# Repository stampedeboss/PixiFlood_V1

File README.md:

THIS REPOSITORY HAS BEEN REPLACED WITH A NEW VERSION COVERING MULTIPLE VERSIONS

# PixiFlood
PixiFlood LED Driver, Turn your 10W Floodlight into a WS2811 Pixel

DESCRIPTION
A LED Driver that will allow a 10W flood light to be controlled as a WS2811 Pixel. Allows up to 
170 flood lights to be controlled with a single universe. Design includes 3 variations: 
o Plated Through Hole 
o SMT 
o Integrated nRF24 Wireless Controller 

My goal was to enable placement of a flood light without having to deal with different controllers or 
wiring needs. By using WS2811, place a flood light at the beginning or end of a pixel string and maintain 
complete control. 

The additional wireless version allows the driver to function as its own controller and communicate 
via wireless connection using the Komby Protocol. It contains an ATMEGA328 and necessary circuitry to 
support the nRF24 and Komby Software. 

Designed for LED Modules: 
Model: 10W 
Color: RGB 
DC Forward Voltage (VF): Red 6-8V, Green 9-12V, Blue 9-12V 
DC Forward current (IF): 300MA 
Out put Lumens: Red 120-150LM, Green 200-300LM, Blue 70-100LM 
Wave Length : Red 620-625nm , Green 515-520nm, Blue

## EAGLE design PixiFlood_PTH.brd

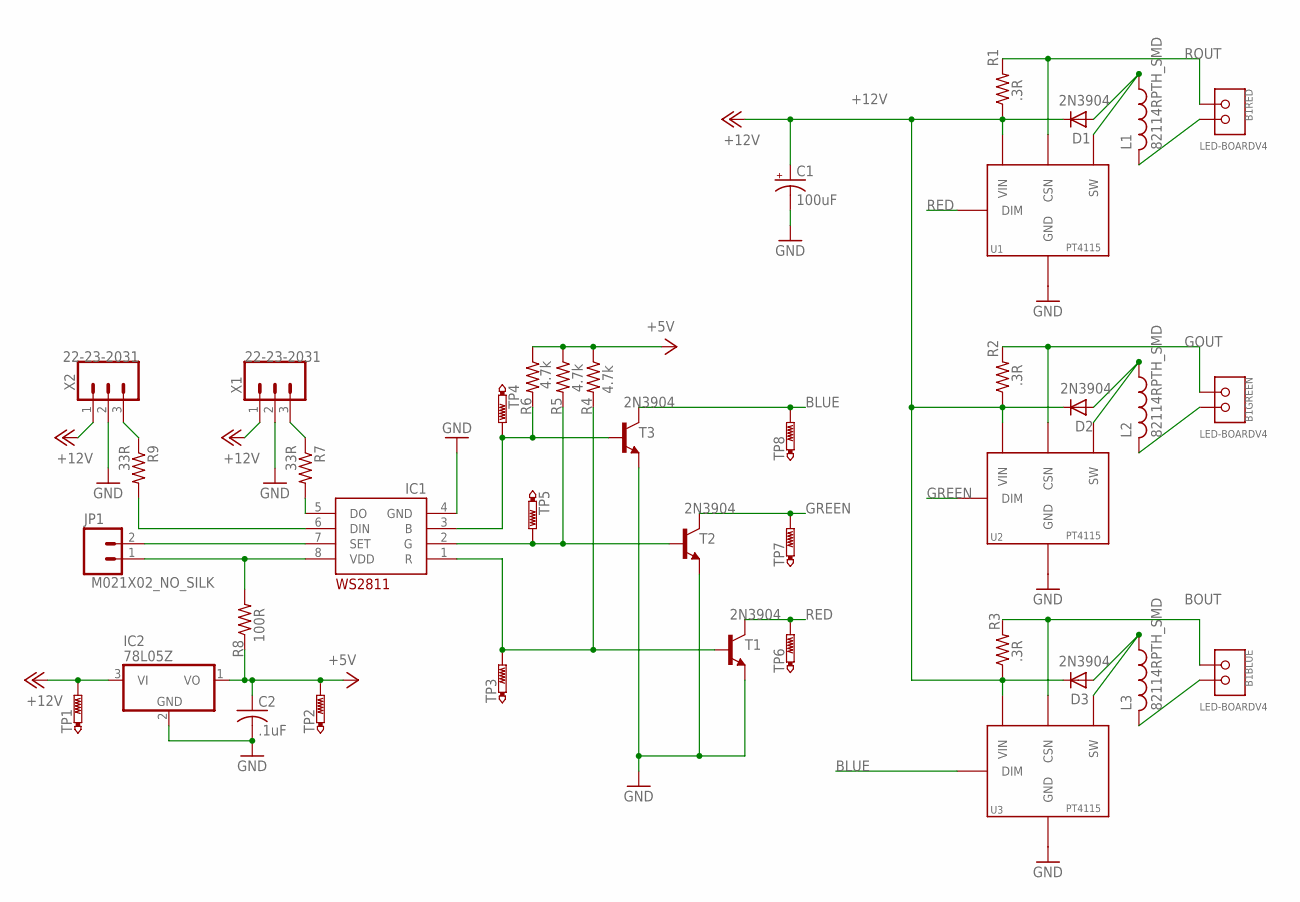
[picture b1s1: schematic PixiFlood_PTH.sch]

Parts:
B1: LED-BOARDV4; LED_BOARD-V4
C1: 100uF; TT2D6L
C2: .1uF; C050-024X044
D1, D2, D3: 2N3904; DO07
IC1: WS2811-SOP8; SO08-SKINNYPADS
IC2: 78L05Z; TO92
JP1: M021X02_NO_SILK; 1X02_NO_SILK
L1, L2, L3: 82114RPTH_SMD; INDUCTOR
R1, R2, R3: .3R; 0204/7
R4, R5, R6: 4.7k; 0204/7
R7, R9: 33R; 0204/7
R8: 100R; 0204/7
T1, T2, T3: 2N3904; TO92
TP1, TP2: PTR1B2,54; B2,54
TP3, TP4, TP5, TP6, TP7, TP8: PTR1B1,27; B1,27
U1, U2, U3: PT4115B89E; SOT89-5
X1, X2: 22-23-2031

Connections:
+5V: C2.1, IC2.1 (VO), R4.1, R5.1, R6.1, R8.1, TP2.TP
+12V: C1.+, D1.C, D2.C, D3.C, IC2.3 (VI), R1.1, R2.1, R3.1, TP1.TP, U1.5 (VIN), U2.5 (VIN), U3.5 (VIN), X1.1, X2.1
BLUE: T3.1 (C), TP8.TP, U3.3 (DIM)
BOUT: B1.B+, B1.B+@2, R3.2, U3.4 (CSN)
GND: C1.-, C2.2, IC1.4 (GND), IC2.2 (GND), T1.3 (E), T2.3 (E), T3.3 (E), U1.2 (GND), U1.2@1 (GND), U1.2@2 (GND), U1.2@3 (GND), U2.2 (GND), U2.2@1 (GND), U2.2@2 (GND), U2.2@3 (GND), U3.2 (GND), U3.2@1 (GND), U3.2@2 (GND), U3.2@3 (GND), X1.2, X2.2
GOUT: B1.G+, B1.G+@1, R2.2, U2.4 (CSN)
GREEN: T2.1 (C), TP7.TP, U2.3 (DIM)
unnamed: D1.A, L1.1, L1.1@A (1), U1.1 (SW)
unnamed: D3.A, L3.1, L3.1@A (1), U3.1 (SW)
unnamed: B1.R-, B1.R-@1, L1.2, L1.2@A (2)
unnamed: R7.1, X1.3
unnamed: D2.A, L2.1, L2.1@A (1), U2.1 (SW)
unnamed: R9.1, X2.3
unnamed: IC1.5 (DO), R7.2
unnamed: IC1.6 (DIN), R9.2
unnamed: B1.G-, B1.G-@1, L2.2, L2.2@A (2)
unnamed: B1.B-, B1.B-@1, L3.2, L3.2@A (2)
unnamed: IC1.3 (B), R6.2, T3.2 (B), TP4.TP
unnamed: IC1.7 (SET), JP1.2
unnamed: IC1.2 (G), R5.2, T2.2 (B), TP5.TP
unnamed: IC1.1 (R), R4.2, T1.2 (B), TP3.TP
RED: T1.1 (C), TP6.TP, U1.3 (DIM)
ROUT: B1.R+, B1.R+@1, R1.2, U1.4 (CSN)
VDD: IC1.8 (VDD), JP1.1, R8.2

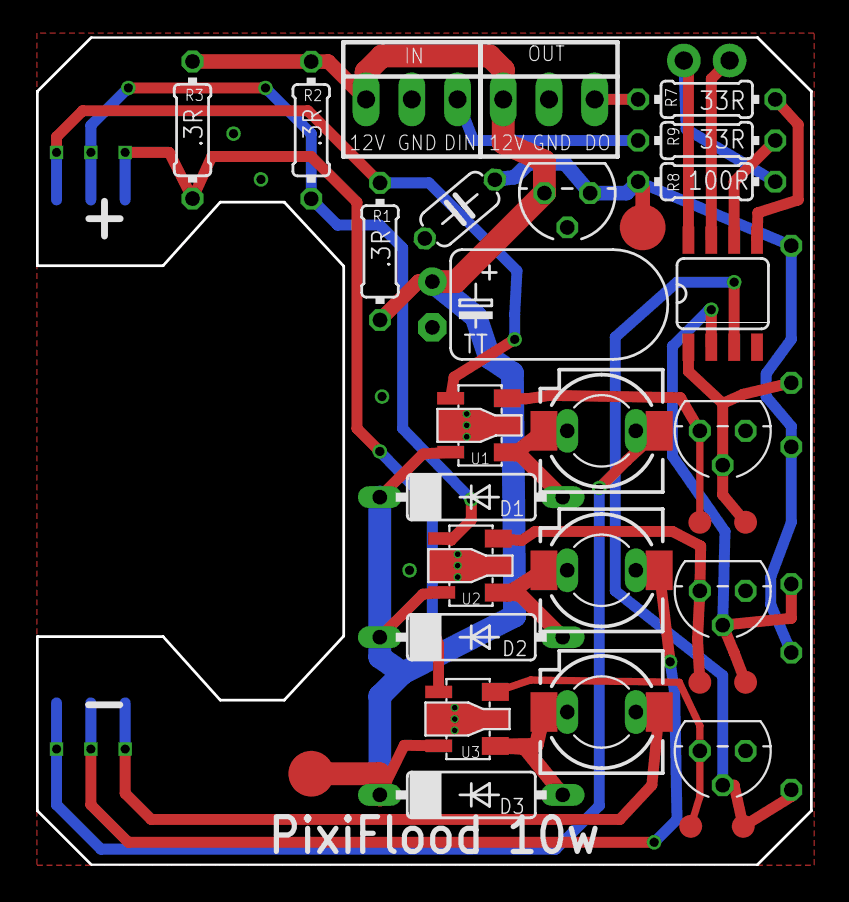
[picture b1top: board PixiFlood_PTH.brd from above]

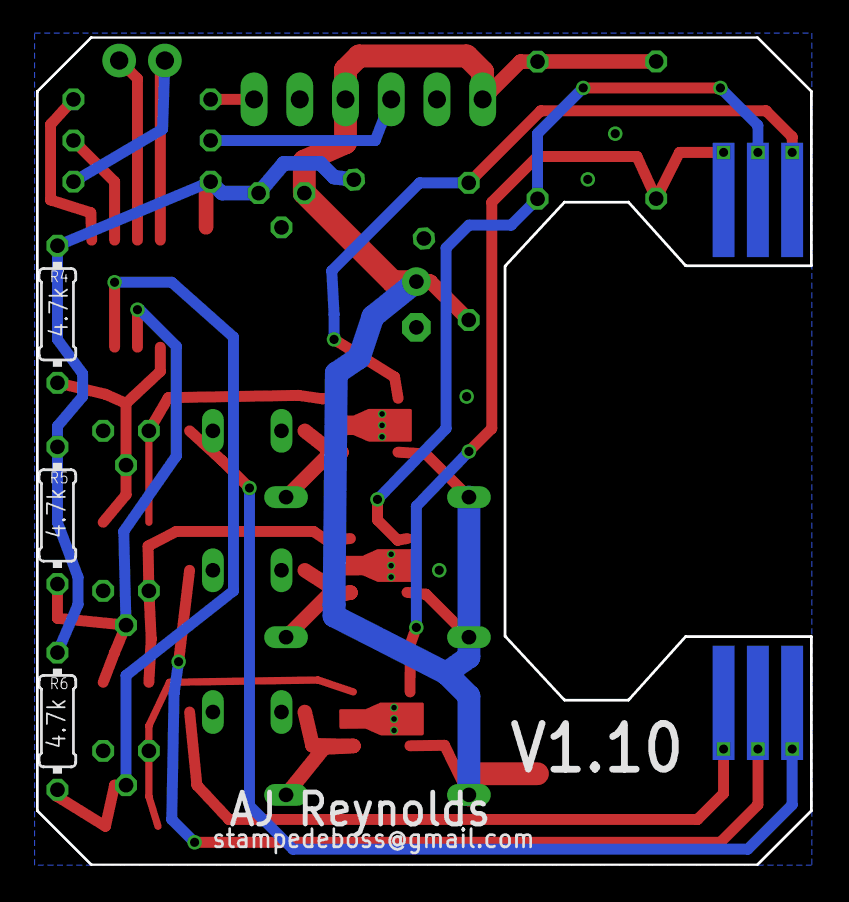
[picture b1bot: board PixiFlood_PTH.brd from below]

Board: 2 copper layers, 43.0 x 46.0 mm, 37 parts (3 on the bottom side), 24 nets.

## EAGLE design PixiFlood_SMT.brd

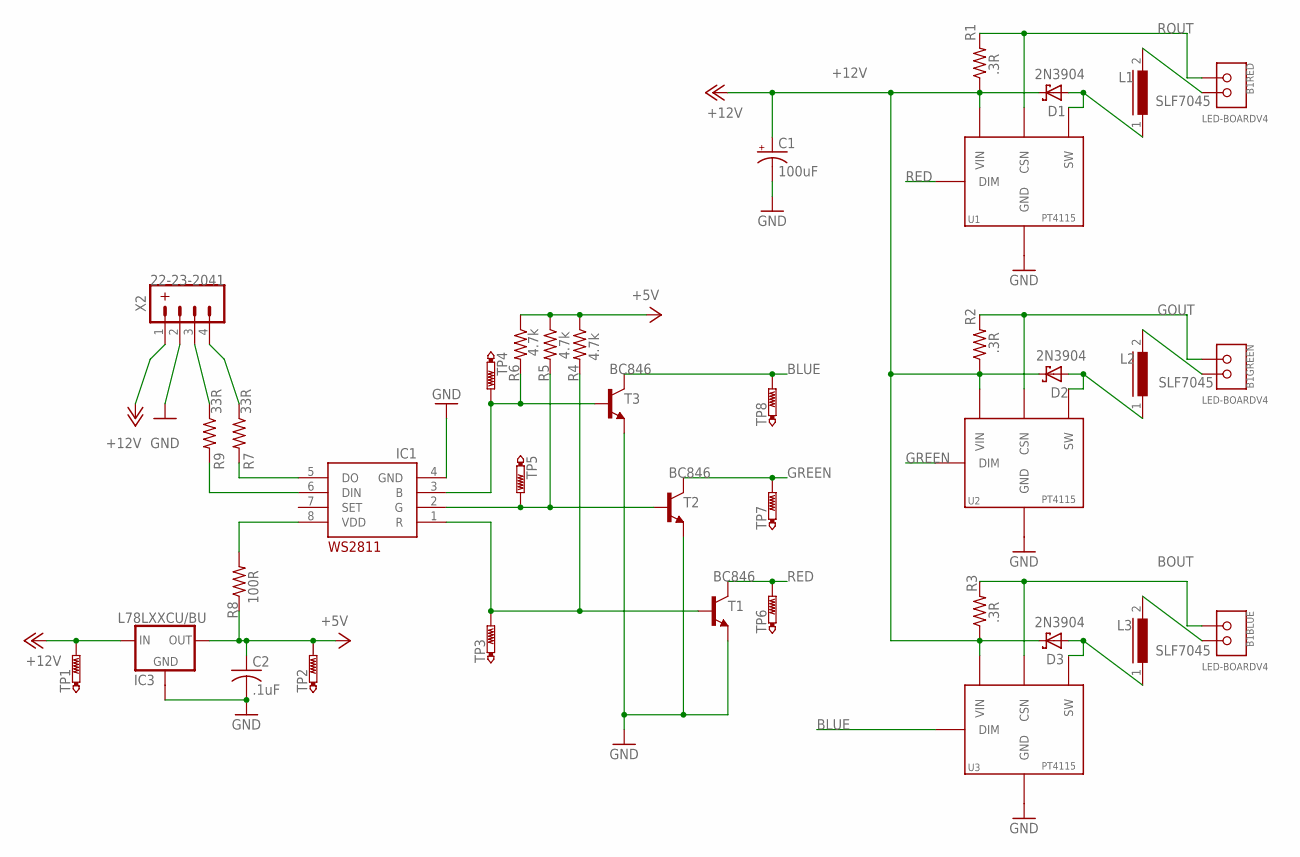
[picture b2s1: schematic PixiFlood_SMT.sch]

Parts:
B1: LED-BOARDV4; LED_BOARD-V4
C1: 100uF; TT2D6L
C2: .1uF; C0805
D1, D2, D3: 2N3904; SMA-DO214AC
IC1: WS2811-SOP8; SO08-SKINNYPADS
IC3: L78LXXCU/BU; SOT89
L1, L2, L3: SLF7045
R1, R2, R3: .3R; R1206
R4, R5, R6: 4.7k; R0805
R7: 33R; M0805
R8: 100R; R0805
R9: 33R; R0805
T1, T2, T3: BC846; SOT23
TP1: PTR1TP20SQ; TP20SQ
TP2: PTR1TP20R; TP20R
TP3, TP4, TP5, TP6, TP7, TP8: PTR1B1,27; B1,27
U1, U2, U3: PT4115B89E; SOT89-5
X2: 22-23-2041

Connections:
+5V: C2.1, IC3.1 (OUT), R4.1, R5.1, R6.1, R8.1, TP2.TP
+12V: C1.+, D1.K (C), D2.K (C), D3.K (C), IC3.3 (IN), R1.1, R2.1, R3.1, TP1.TP, U1.5 (VIN), U2.5 (VIN), U3.5 (VIN), X2.1
BLUE: T3.3 (C), TP8.TP, U3.3 (DIM)
BOUT: B1.B+, B1.B+@2, R3.2, U3.4 (CSN)
GND: C1.-, C2.2, IC1.4 (GND), IC3.4 (GND1), T1.2 (E), T2.2 (E), T3.2 (E), U1.2 (GND), U1.2@1 (GND), U1.2@2 (GND), U1.2@3 (GND), U2.2 (GND), U2.2@1 (GND), U2.2@2 (GND), U2.2@3 (GND), U3.2 (GND), U3.2@1 (GND), U3.2@2 (GND), U3.2@3 (GND), X2.2
GOUT: B1.G+, B1.G+@1, R2.2, U2.4 (CSN)
GREEN: T2.3 (C), TP7.TP, U2.3 (DIM)
unnamed: D1.A, L1.1, U1.1 (SW)
unnamed: D3.A, L3.1, U3.1 (SW)
unnamed: B1.R-, B1.R-@1, L1.2
unnamed: R7.1, X2.4
unnamed: D2.A, L2.1, U2.1 (SW)
unnamed: R9.1, X2.3
unnamed: IC1.5 (DO), R7.2
unnamed: IC1.6 (DIN), R9.2
unnamed: B1.G-, B1.G-@1, L2.2
unnamed: B1.B-, B1.B-@1, L3.2
unnamed: IC1.3 (B), R6.2, T3.1 (B), TP4.TP
unnamed: IC1.2 (G), R5.2, T2.1 (B), TP5.TP
unnamed: IC1.1 (R), R4.2, T1.1 (B), TP3.TP
RED: T1.3 (C), TP6.TP, U1.3 (DIM)
ROUT: B1.R+, B1.R+@1, R1.2, U1.4 (CSN)
VDD: IC1.8 (VDD), R8.2

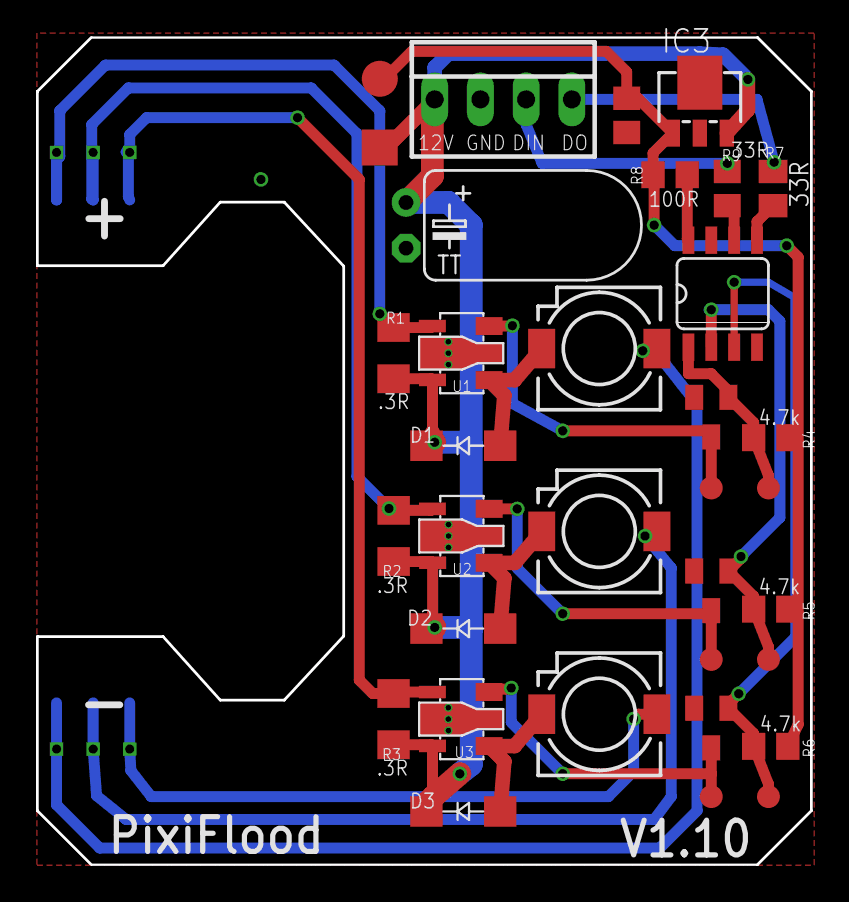
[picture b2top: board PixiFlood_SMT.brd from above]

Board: 2 copper layers, 43.0 x 46.0 mm, 35 parts (0 on the bottom side), 23 nets.

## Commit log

2015-08-06 initial project version
2015-08-06 Cleaned up initial setup
2015-08-06 Reorging into Branches
2015-08-06 Version 9 of the Driver
2015-08-06 Removed files not related to Version 9
2015-08-06 added .gitignore
2015-08-06 Added .gitignore file
2015-08-06 Version 10 of the Driver ******** WORK IN PROGRESS ***********
2015-08-06 Additional details in Change Log
2015-08-06 additions to .gitignore
2015-08-27 added 20w board
2015-08-28 moved archive to version for save

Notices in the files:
parts and their libraries:
SparkFun-Connectors: Licensing: Creative Commons ShareAlike 4.0 International - https://creativecommons.org/licenses/by-sa/4.0
